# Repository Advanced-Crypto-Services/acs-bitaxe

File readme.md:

# **Based on the Bitaxe project**
## https://github.com/skot/bitaxe

# FIRST BATCH OF PCBS ORDERED 11/27/24

# Current Models
## Bitaxe Ultra 204 Modified for 800x480 add-on

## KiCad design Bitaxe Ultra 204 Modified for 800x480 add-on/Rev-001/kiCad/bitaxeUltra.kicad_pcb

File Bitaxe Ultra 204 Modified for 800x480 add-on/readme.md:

```
Open Source is Intrinsic to Bitcoin
```
# The bitaxeUltra
bitaxe is a fully open source hardware Bitcoin ASIC miner. Ultra is the 3rd major revision of the bitaxe that now includes the BM1366 ASIC from the S19XP

## Bitaxe Ultra 204 Modified for 800x480 add-on
- **This model is based on the Bitaxe Ultra 204 model, but modified for the 800x480 resolution of the add-on. Used with the following projects:**
- https://github.com/Advanced-Crypto-Services/acs-esp-miner
- https://github.com/Advanced-Crypto-Services/acs-bitaxe-lcd-800x480

### Modifications: 
- Added addtional i2C pins for the 800x480 LCD
- Added 4.7k pull-up resistors to the i2C pins for better signal integrity
- Added 5V_OUT for powering the LCD
- Added a Fuse on both 5V_OUT and V_IN
- Added third heatsink mounting hole for better stability with Tower Cooler
- Changed the BOOT and RESET buttons to 90 degree angled buttons for better access when inside and enclosure

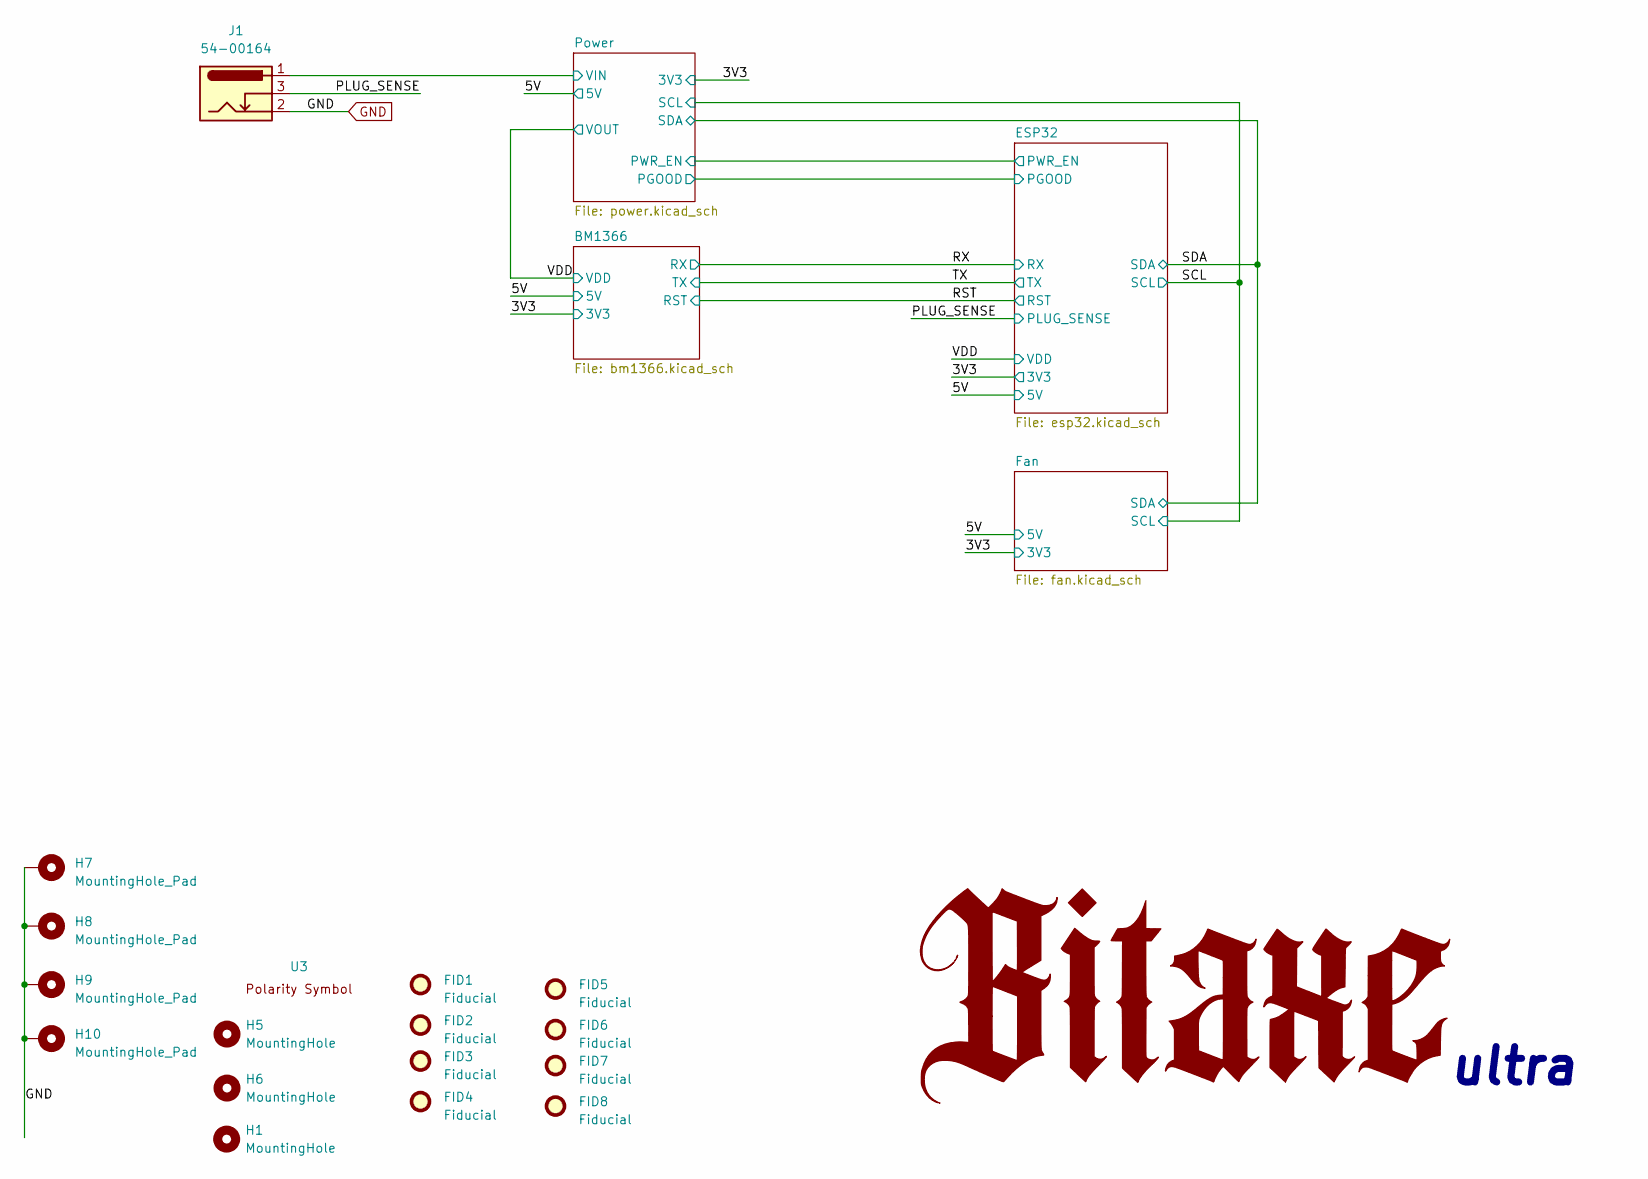
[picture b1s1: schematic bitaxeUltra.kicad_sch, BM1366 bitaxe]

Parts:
FID1, FID2, FID3, FID4, FID5, FID6, FID7, FID8: Fiducial; Fiducial_1mm_Mask2mm
H1, H5, H6: MountingHole; MountingHole_3.5mm
H7, H8, H9, H10: MountingHole_Pad; MountingHole_3mm_Pad_Via
J1: 54-00164; BarrelJack_Wuerth_694106106102_2.0x5.5mm; PARTNO 54-00164
U3: polarity

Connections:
/PLUG_SENSE: J1.3; also elsewhere on the board
/Power/VIN: J1.1; also elsewhere on the board
GND: H7.1, H8.1, H9.1, H10.1, J1.2; also elsewhere on the board

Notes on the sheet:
ultra

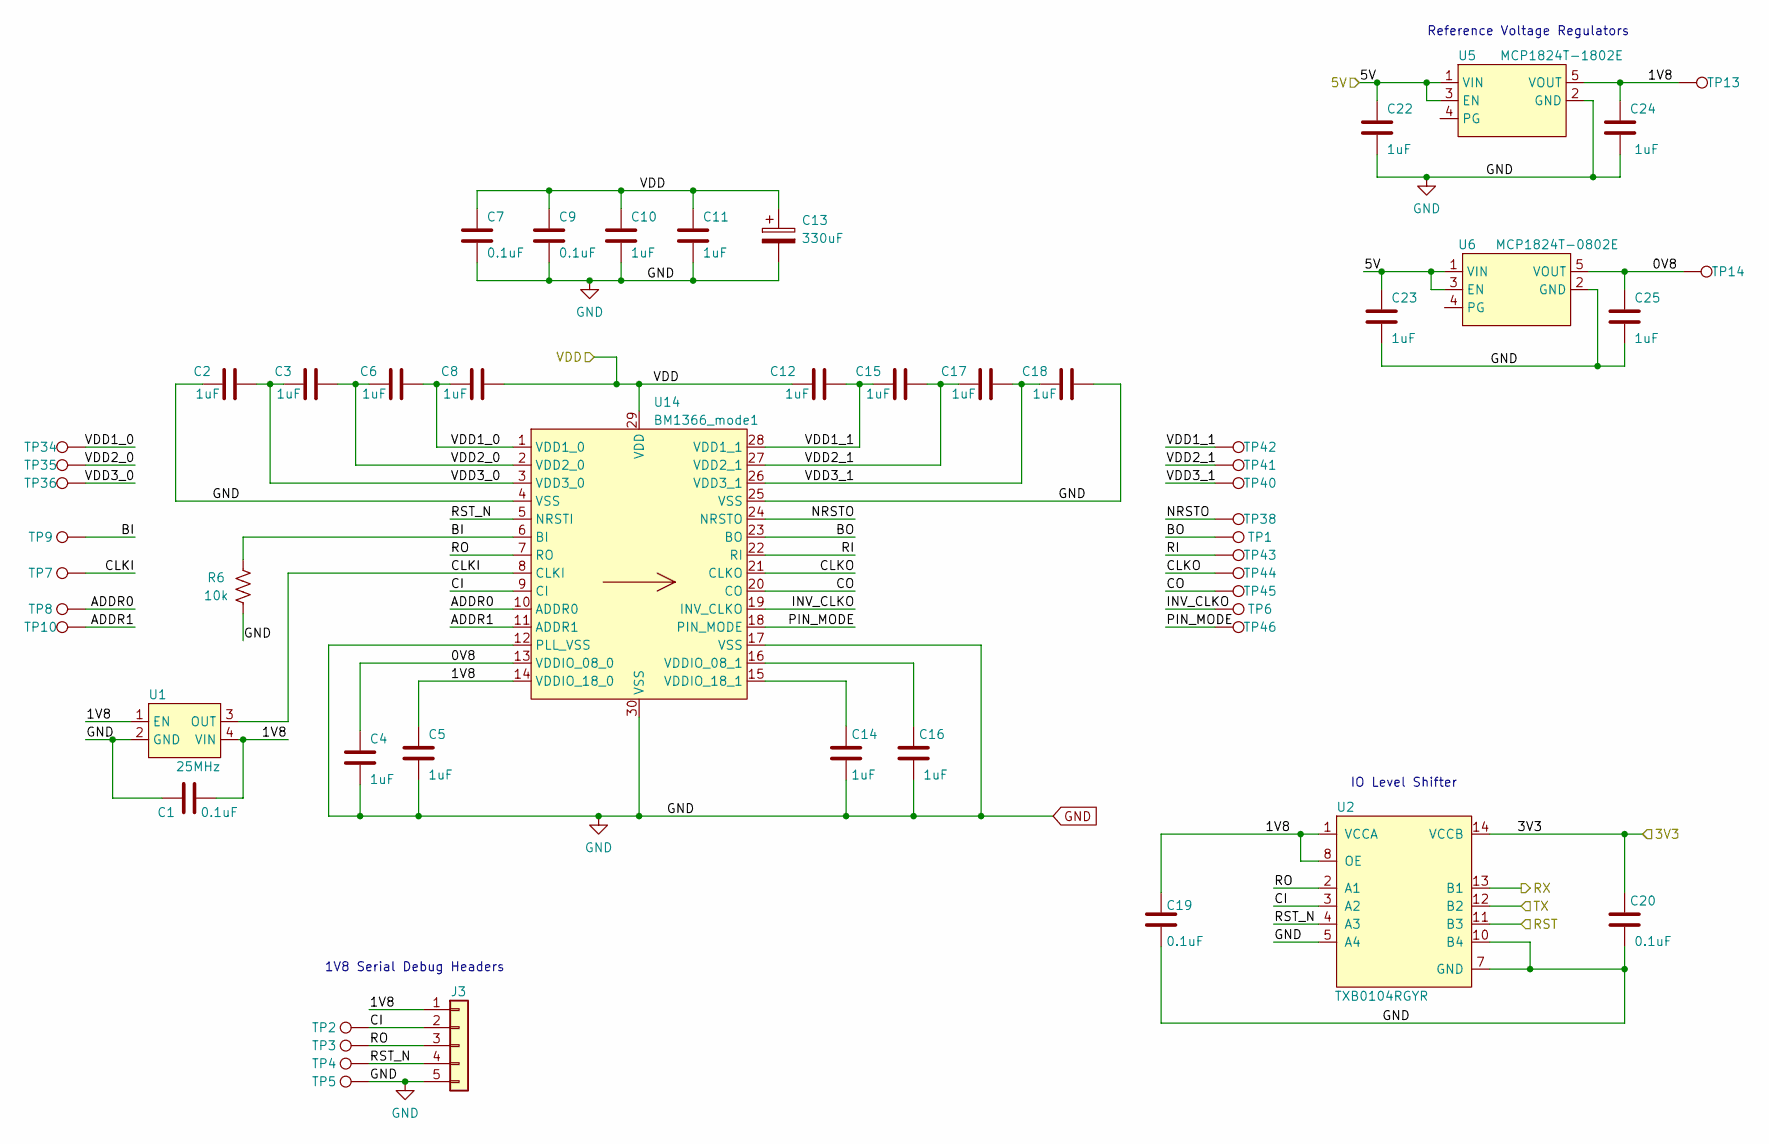
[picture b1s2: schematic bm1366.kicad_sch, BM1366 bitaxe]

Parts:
C1, C7, C9, C19, C20: 0.1uF; C_0402_1005Metric; PARTNO 0402X104K100CT
C2, C3, C4, C5, C6, C8, C10, C11, C12, C14, C15, C16, C17, C18, C22, C23, C24, C25: 1uF; C_0402_1005Metric; PARTNO EMK105BJ105MV-F
C13: 330uF; CP_EIA-7343-31_Kemet-D_Pad2.25x2.55mm_HandSolder; PARTNO 293D337X9010E2TE3
J3: Conn_01x05; PinHeader_1x05_P2.54mm_Vertical
R6: 10k; R_0402_1005Metric; PARTNO RC0402JR-0710KL
TP1, TP2, TP3, TP4, TP5, TP6, TP7, TP8, TP9, TP10, TP13, TP14, TP34, TP35, TP36, TP38, TP40, TP41, TP42, TP43, TP44, TP45, TP46: TestPoint; TestPoint_Pad_D1.5mm
U1: 25MHz; O 25,0-JO32-B-1V3-1-T1-LF; PARTNO O 25,0-JO32-B-1V3-1-T1-LF
U2: TXB0104RGYR; TXB0104; PARTNO TXB0104RGYR
U5: MCP1824T-1802E; SOT-23-5; PARTNO MCP1824T-1802E/OT
U6: MCP1824T-0802E; SOT-23-5; PARTNO MCP1824T-0802E/OT
U14: BM1366_mode1; BM1366

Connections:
/3V3: C20.1, U2.14 (VCCB); also elsewhere on the board
/5V: C22.1, C23.1, U5.1 (VIN), U5.3 (EN), U6.1 (VIN), U6.3 (EN); also elsewhere on the board
/BM1366/0V8: C4.1, C25.1, TP14.1, U6.5 (VOUT), U14.13 (VDDIO_08_0)
/BM1366/1V8: C1.2, C5.1, C19.1, C24.1, J3.1, TP13.1, U1.1 (EN), U1.4 (VIN), U2.1 (VCCA), U2.8 (OE), U5.5 (VOUT), U14.14 (VDDIO_18_0)
/BM1366/ADDR0: TP8.1, U14.10 (ADDR0)
/BM1366/ADDR1: TP10.1, U14.11 (ADDR1)
/BM1366/BI: R6.2, TP9.1, U14.6 (BI)
/BM1366/BO: TP1.1, U14.23 (BO)
/BM1366/CI: J3.2, TP2.1, U2.3 (A2), U14.9 (CI)
/BM1366/CLKI: TP7.1, U1.3 (OUT), U14.8 (CLKI)
/BM1366/CLKO: TP44.1, U14.21 (CLKO)
/BM1366/CO: TP45.1, U14.20 (CO)
/BM1366/INV_CLKO: TP6.1, U14.19 (INV_CLKO)
/BM1366/NRSTO: TP38.1, U14.24 (NRSTO)
/BM1366/PIN_MODE: TP46.1, U14.18 (PIN_MODE)
/BM1366/RI: TP43.1, U14.22 (RI)
/BM1366/RO: J3.3, TP3.1, U2.2 (A1), U14.7 (RO)
/BM1366/RST_N: J3.4, TP4.1, U2.4 (A3), U14.5 (NRSTI)
/BM1366/VDD1_0: C6.2, C8.1, TP34.1, U14.1 (VDD1_0)
/BM1366/VDD1_1: C12.2, C15.1, TP42.1, U14.28 (VDD1_1)
/BM1366/VDD2_0: C3.2, C6.1, TP35.1, U14.2 (VDD2_0)
/BM1366/VDD2_1: C15.2, C17.1, TP41.1, U14.27 (VDD2_1)
/BM1366/VDD3_0: C2.2, C3.1, TP36.1, U14.3 (VDD3_0)
/BM1366/VDD3_1: C17.2, C18.1, TP40.1, U14.26 (VDD3_1)
/RST: U2.11 (B3); also elsewhere on the board
/RX: U2.13 (B1); also elsewhere on the board
/TX: U2.12 (B2); also elsewhere on the board
/VDD: C7.1, C8.2, C9.1, C10.1, C11.1, C12.1, C13.1, U14.29 (VDD); also elsewhere on the board
GND: C1.1, C2.1, C4.2, C5.2, C7.2, C9.2, C10.2, C11.2, C13.2, C14.2, C16.2, C18.2, C19.2, C20.2, C22.2, C23.2, C24.2, C25.2, J3.5, R6.1, TP5.1, U1.2 (GND), U2.5 (A4), U2.7 (GND), U2.10 (B4), U2.15 (GND), U2.16 (GND), U2.17 (GND), U2.18 (GND), U2.19 (GND), U5.2 (GND), U6.2 (GND), U14.4 (VSS), U14.12 (PLL_VSS), U14.17 (VSS), U14.25 (VSS), U14.30 (VSS); also elsewhere on the board
unnamed: C16.1, U14.16 (VDDIO_08_1)
unnamed: C14.1, U14.15 (VDDIO_18_1)

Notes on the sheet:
1V8 Serial Debug Headers
Reference Voltage Regulators
IO Level Shifter

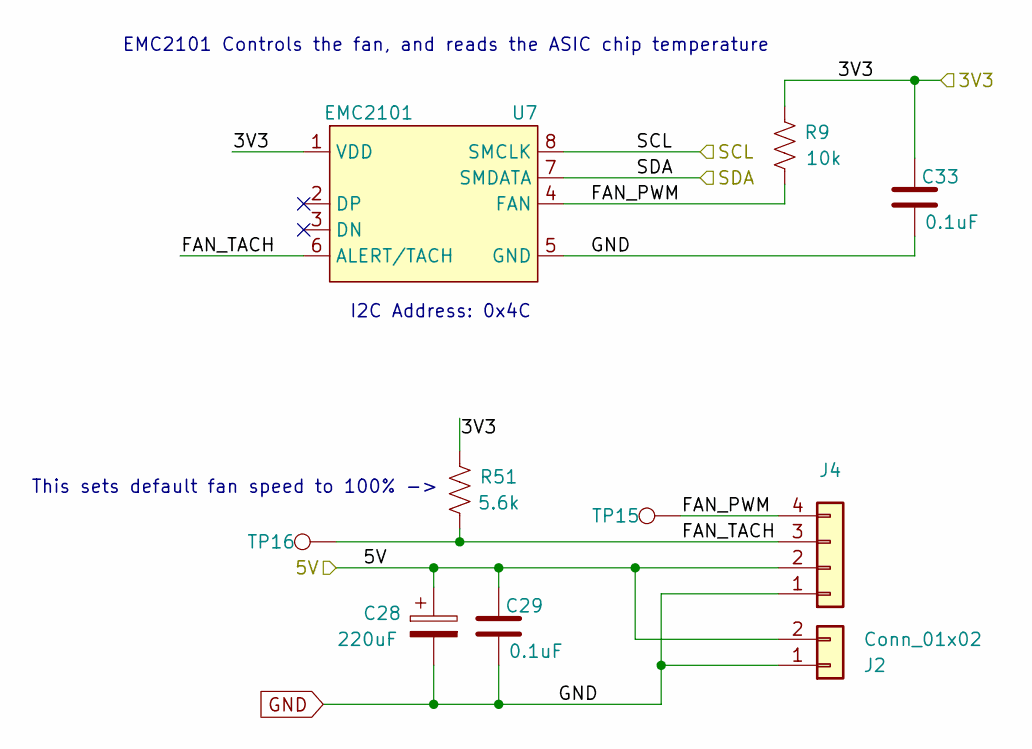
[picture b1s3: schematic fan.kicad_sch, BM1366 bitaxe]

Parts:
C28: 220uF; CP_Elec_6.3x7.7; PARTNO 865080345012
C29, C33: 0.1uF; C_0402_1005Metric; PARTNO 0402X104K100CT
J2: Conn_01x02; JST_XH_B2B-XH-A_1x02_P2.50mm_Vertical; PARTNO B2B-XH-A
J4: Conn_01x04; 470531000; PARTNO 0470531000
R9: 10k; R_0402_1005Metric; PARTNO RC0402JR-0710KL
R51: 5.6k; R_0402_1005Metric; PARTNO RC0402FR-135K6L
TP15, TP16: TestPoint; TestPoint_Pad_D1.5mm
U7: EMC2101; TSSOP-8_3x3mm_P0.65mm; PARTNO EMC2101-R-ACZL-TR

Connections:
/3V3: C33.1, R9.2, U7.1 (VDD); also elsewhere on the board
/5V: C28.1, C29.1, J2.2, J4.2; also elsewhere on the board
/Fan/FAN_PWM: J4.4, R9.1, TP15.1, U7.4 (FAN)
/Fan/FAN_TACH: J4.3, TP16.1, U7.6 (ALERT/TACH); also elsewhere on the board
/SCL: U7.8 (SMCLK); also elsewhere on the board
/SDA: U7.7 (SMDATA); also elsewhere on the board
GND: C28.2, C29.2, C33.2, J2.1, J4.1, U7.5 (GND); also elsewhere on the board

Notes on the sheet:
EMC2101 Controls the fan, and reads the ASIC chip temperature
This sets default fan speed to 100% ->
I2C Address: 0x4C

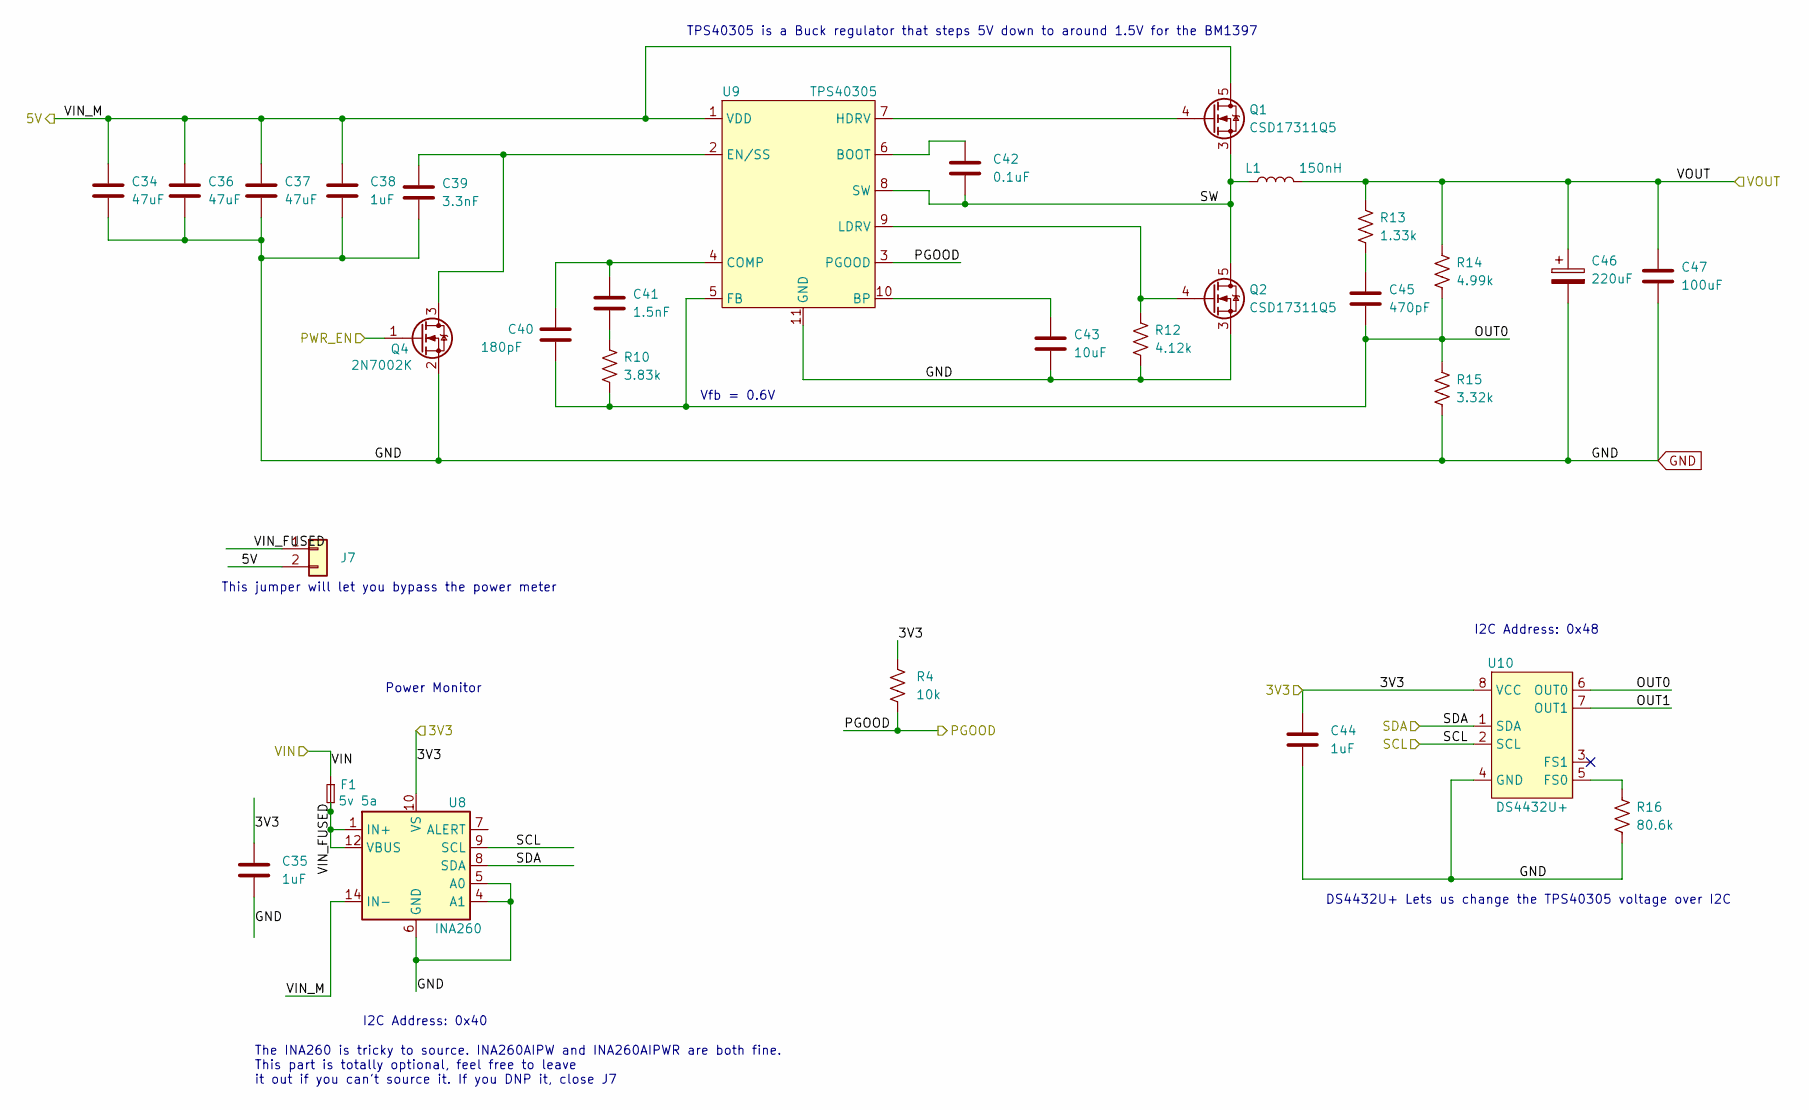
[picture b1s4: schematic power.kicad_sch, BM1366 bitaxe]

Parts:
C34, C36, C37: 47uF; C_1210_3225Metric; PARTNO GRM32ER61C476KE15L
C35, C44: 1uF; C_0402_1005Metric; PARTNO EMK105BJ105MV-F
C38: 1uF; C_0402_1005Metric; PARTNO CL21B105KOFNNNG
C39: 3.3nF; C_0402_1005Metric; PARTNO CL05B332KB5NNNC
C40: 180pF; C_0805_2012Metric; PARTNO CC0805JRNPO9BN181
C41: 1.5nF; C_0805_2012Metric; PARTNO CC0805KRX7R9BB152
C42: 0.1uF; C_0402_1005Metric; PARTNO 0402X104K100CT
C43: 10uF; C_0805_2012Metric; PARTNO CL21A106KOQNNNE
C45: 470pF; C_0805_2012Metric; PARTNO 0805B471K500CT
C46: 220uF; CAP_2R5TPE220MAFB; PARTNO 2R5TPE220MAFB
C47: 100uF; C_1206_3216Metric; PARTNO C3216X5R0J107M160AB
F1: 5v 5a; Fuse_0603_1608Metric
J7: Conn_01x02; PinHeader_1x02_P2.54mm_Vertical
L1: 150nH; FP1005R1-R15-R; PARTNO FP1005R1-R15-R
Q1, Q2: CSD17311Q5; PARTNO CSD17311Q5
Q4: 2N7002K; SOT-323_SC-70; PARTNO 2N7002KW
R4: 10k; R_0402_1005Metric; PARTNO RC0402JR-0710KL
R10: 3.83k; R_0402_1005Metric; PARTNO RC0402FR-073K83L
R12: 4.12k; R_0402_1005Metric; PARTNO RMCF0402FT4K12
R13: 1.33k; R_0402_1005Metric; PARTNO RC0402FR-071K33L
R14: 4.99k; R_0402_1005Metric; PARTNO RC0402FR-074K99L
R15: 3.32k; R_0402_1005Metric; PARTNO RC0402FR-073K32L
R16: 80.6k; R_0402_1005Metric; PARTNO RC0402FR-0780K6L
U8: INA260; TSSOP-16_4.4x5mm_P0.65mm; PARTNO INA260AIPW
U9: TPS40305; PARTNO TPS40305DRCR
U10: DS4432U+; TSSOP-8_3x3mm_P0.65mm; PARTNO DS4432U+

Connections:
/3V3: C35.1, C44.1, R4.1, U8.10 (VS), U10.8 (VCC); also elsewhere on the board
/5V: C34.1, C36.1, C37.1, C38.1, J7.2, Q1.5 (D), U8.14 (IN-), U8.15 (IN-), U8.16 (IN-), U9.1 (VDD); also elsewhere on the board
/ESP32/PWR_EN: Q4.1 (G); also elsewhere on the board
/Power/OUT0: C40.2, C45.2, R10.2, R14.2, R15.1, U9.5 (FB), U10.6 (OUT0)
/Power/OUT1: U10.7 (OUT1)
/Power/PGOOD: R4.2, U9.3 (PGOOD); also elsewhere on the board
/Power/SW: C42.2, L1.1, Q1.1, Q1.2, Q1.3 (S), Q2.5 (D), U9.8 (SW)
/Power/VIN: F1.1; also elsewhere on the board
/Power/VIN_FUSED: F1.2, J7.1, U8.1 (IN+), U8.2 (IN+), U8.3 (IN+), U8.12 (VBUS)
/SCL: U8.9 (SCL), U10.2 (SCL); also elsewhere on the board
/SDA: U8.8 (SDA), U10.1 (SDA); also elsewhere on the board
/VDD: C46.1, C47.1, L1.2, R13.1, R14.1; also elsewhere on the board
GND: C34.2, C35.2, C36.2, C37.2, C38.2, C39.2, C43.2, C44.2, C46.2, C47.2, Q2.1, Q2.2, Q2.3 (S), Q4.2 (S), R12.2, R15.2, R16.2, U8.4 (A1), U8.5 (A0), U8.6 (GND), U8.11 (GND), U9.11 (GND), U10.4 (GND); also elsewhere on the board
unnamed: C41.2, R10.1
unnamed: C45.1, R13.2
unnamed: Q1.4 (G), U9.7 (HDRV)
unnamed: Q2.4 (G), R12.1, U9.9 (LDRV)
unnamed: C39.1, Q4.3 (D), U9.2 (EN/SS)
unnamed: C42.1, U9.6 (BOOT)
unnamed: C43.1, U9.10 (BP)
unnamed: C40.1, C41.1, U9.4 (COMP)
unnamed: R16.1, U10.5 (FS0)

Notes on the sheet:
DS4432U+ Lets us change the TPS40305 voltage over I2C
I2C Address: 0x48
The INA260 is tricky to source. INA260AIPW and INA260AIPWR are both fine. This part is totally optional, feel free to leave it out if you can't source it. If you DNP it, close J7
Power Monitor
TPS40305 is a Buck regulator that steps 5V down to around 1.5V for the BM1397
I2C Address: 0x40
Vfb = 0.6V
This jumper will let you bypass the power meter

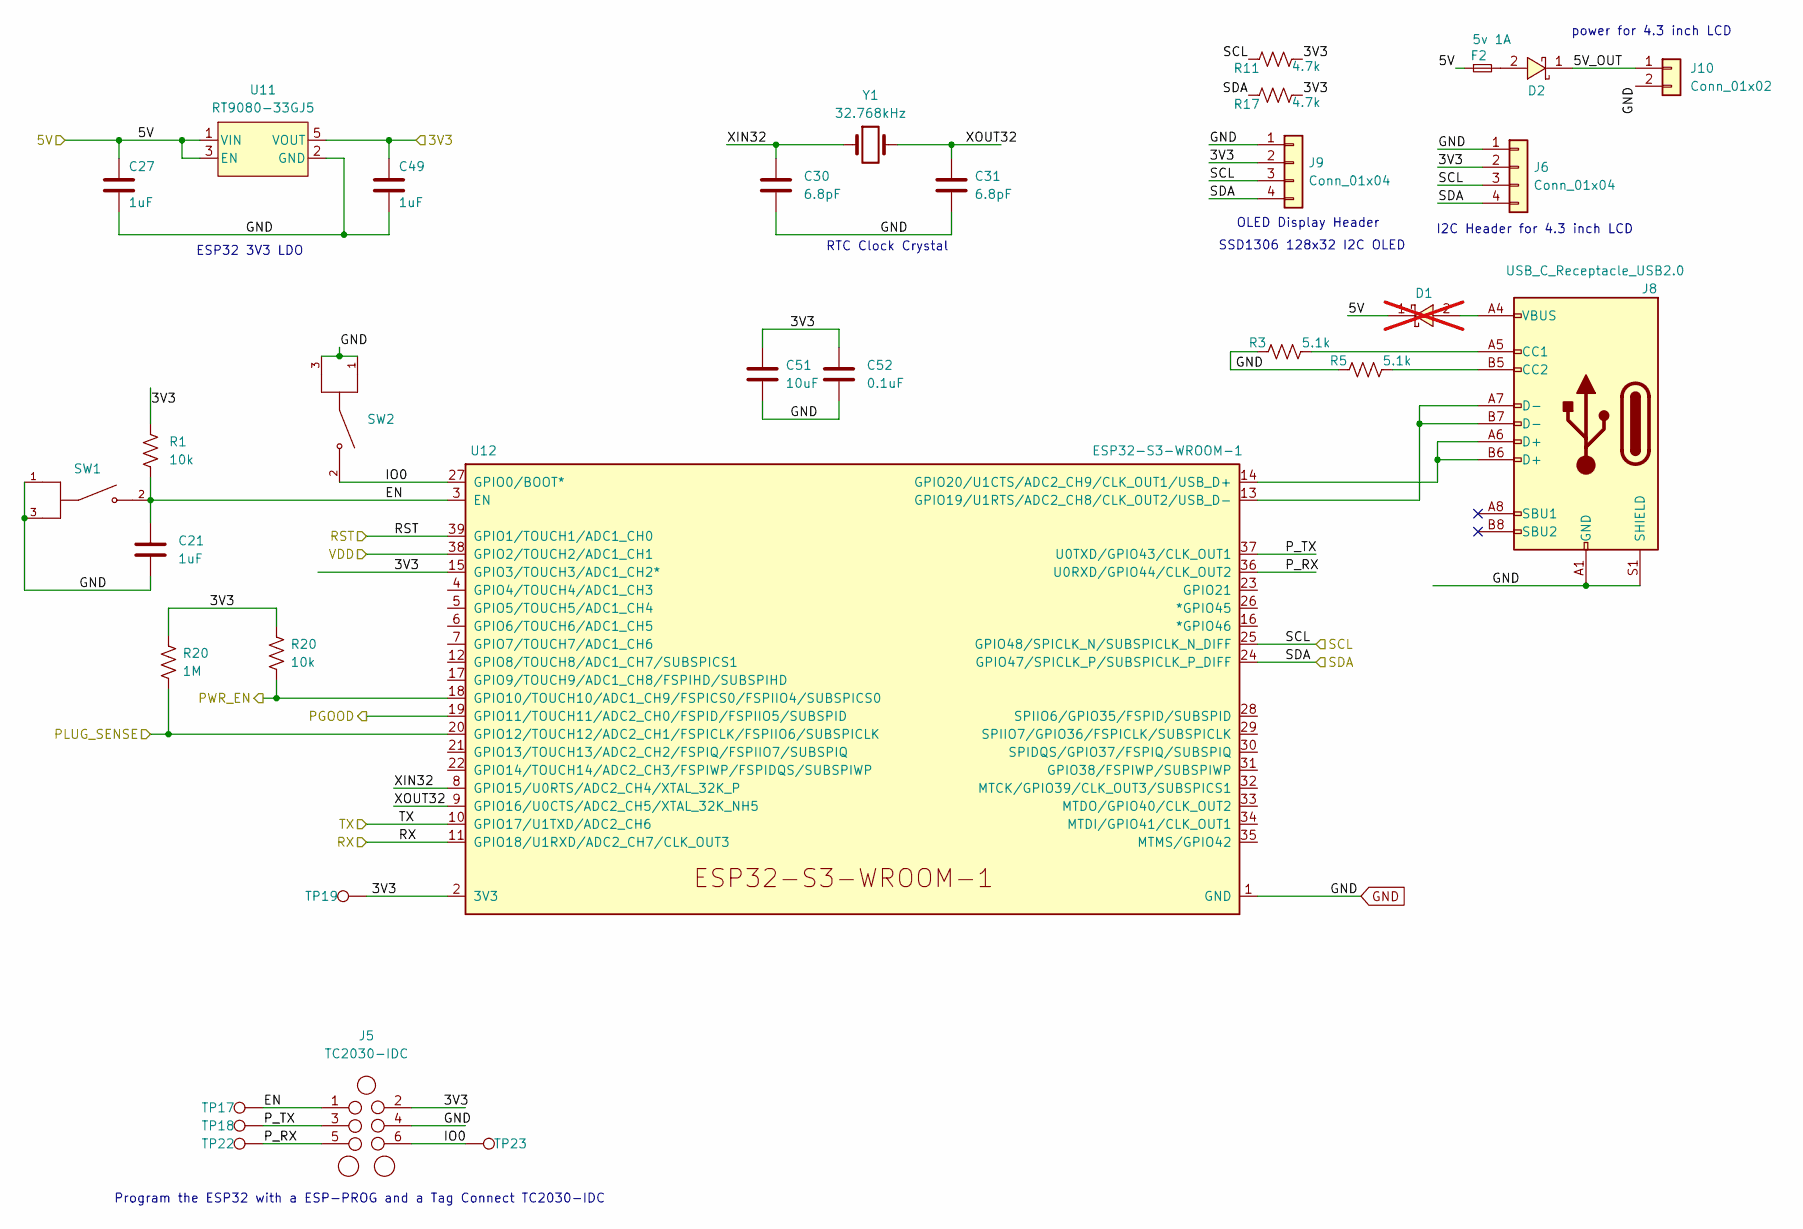
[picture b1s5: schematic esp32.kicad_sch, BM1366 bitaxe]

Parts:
C21, C27, C49: 1uF; C_0402_1005Metric; PARTNO EMK105BJ105MV-F
C30, C31: 6.8pF; C_0402_1005Metric; PARTNO C0402C689C5GAC7867
C51: 10uF; C_0805_2012Metric; PARTNO CL21A106KOQNNNE
C52: 0.1uF; C_0402_1005Metric; PARTNO 0402X104K100CT
D1: SS310; D_SMA; PARTNO SK310A-LTP; not fitted
D2: SS310; D_SMA; PARTNO SK310A-LTP
F2: 5v 1A; Fuse_0603_1608Metric
J5: TC2030-IDC; Tag-Connect_TC2030-IDC-NL_2x03_P1.27mm_Vertical
J6, J9: Conn_01x04; PinSocket_1x04_P2.54mm_Vertical
J8: USB_C_Receptacle_USB2.0; USB_C_Receptacle_GCT_USB4105-xx-A_16P_TopMnt_Horizontal; PARTNO USB4105-GF-A
J10: Conn_01x02; PinSocket_1x02_P2.54mm_Vertical
R1: 10k; R_0402_1005Metric; PARTNO RC0402JR-0710KL
R3, R5: 5.1k; R_0402_1005Metric; PARTNO RMCF0402JT5K10
R11, R17: 4.7k; R_0402_1005Metric; PARTNO RMCF0402JT5K10
R20: 1M; R_0402_1005Metric; PARTNO RC0402FR-071ML
SW1, SW2: GT-TC029B-H025-L1N; SW_TL3340AF160QG; PARTNO CS1213AGF260
TP17, TP18, TP19, TP22, TP23: TestPoint; TestPoint_Pad_D1.5mm
U11: RT9080-33GJ5; PARTNO RT9080-33GJ5
U12: ESP32-S3-WROOM-1; PARTNO ESP32-S3-WROOM-1-N16R8
Y1: 32.768kHz; SC32S-7PF20PPM; PARTNO SC32S-7PF20PPM

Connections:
/3V3: C49.1, C51.1, C52.1, J5.2, J6.2, J9.2, R1.1, R11.2, R17.2, TP19.1, U11.5 (VOUT), U12.2 (3V3), U12.15 (GPIO3/TOUCH3/ADC1_CH2*); also elsewhere on the board
/5V: C27.1, D1.1, F2.1, U11.1 (VIN), U11.3 (EN); also elsewhere on the board
/ESP32/5V_OUT: D2.1, J10.1
/ESP32/EN: C21.1, J5.1, R1.2, SW1.2, TP17.1, U12.3 (EN)
/ESP32/IO0: J5.6, SW2.2, TP23.1, U12.27 (GPIO0/BOOT*)
/ESP32/PWR_EN: U12.18 (GPIO10/TOUCH10/ADC1_CH9/FSPICS0/FSPIIO4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); also elsewhere on the board
/ESP32/P_RX: J5.5, TP22.1, U12.36 (U0RXD/GPIO44/CLK_OUT2)
/ESP32/P_TX: J5.3, TP18.1, U12.37 (U0TXD/GPIO43/CLK_OUT1)
/ESP32/XIN32: C30.1, U12.8 (GPIO15/U0RTS/ADC2_CH4/XTAL_32K_P), Y1.1
/ESP32/XOUT32: C31.1, U12.9 (GPIO16/U0CTS/ADC2_CH5/XTAL_32K_NH5), Y1.2
/PLUG_SENSE: U12.20 (GPIO12/TOUCH12/ADC2_CH1/FSPICLK/FSPIIO6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); also elsewhere on the board
/Power/PGOOD: U12.19 (GPIO11/TOUCH11/ADC2_CH0/FSPID/FSPIIO5/S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); also elsewhere on the board
/RST: U12.39 (GPIO1/TOUCH1/ADC1_CH0); also elsewhere on the board
/RX: U12.11 (GPIO18/U1RXD/ADC2_CH7/CLK_OUT3); also elsewhere on the board
/SCL: J6.3, J9.3, R11.1, U12.25 (GPIO48/SPICLK_N/SUBSPICLK_N_DIFF); also elsewhere on the board
/SDA: J6.4, J9.4, R17.1, U12.24 (GPIO47/SPICLK_P/SUBSPICLK_P_DIFF); also elsewhere on the board
/TX: U12.10 (GPIO17/U1TXD/ADC2_CH6); also elsewhere on the board
/VDD: U12.38 (GPIO2/TOUCH2/ADC1_CH1); also elsewhere on the board
GND: C21.2, C27.2, C30.2, C31.2, C49.2, C51.2, C52.2, J5.4, J6.1, J8.A1 (GND), J8.A12 (GND), J8.B1 (GND), J8.B12 (GND), J8.S1 (SHIELD), J9.1, J10.2, R3.1, R5.1, SW1.1, SW1.3, SW2.1, SW2.3, U11.2 (GND), U12.1 (GND), U12.40 (GND), U12.41 (GND); also elsewhere on the board
unnamed: D1.2, J8.A4 (VBUS), J8.A9 (VBUS), J8.B4 (VBUS), J8.B9 (VBUS)
unnamed: D2.2, F2.2
unnamed: J8.A5 (CC1), R3.2
unnamed: J8.B5 (CC2), R5.2
unnamed: J8.A7 (D-), J8.B7 (D-), U12.13 (GPIO19/U1RTS/ADC2_CH8/CLK_OUT2/USB_D-)
unnamed: J8.A6 (D+), J8.B6 (D+), U12.14 (GPIO20/U1CTS/ADC2_CH9/CLK_OUT1/USB_D+)

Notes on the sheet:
I2C Header for 4.3 inch LCD
RTC Clock Crystal
ESP32 3V3 LDO
Program the ESP32 with a ESP-PROG and a Tag Connect TC2030-IDC
SSD1306 128x32 I2C OLED
power for 4.3 inch LCD
OLED Display Header

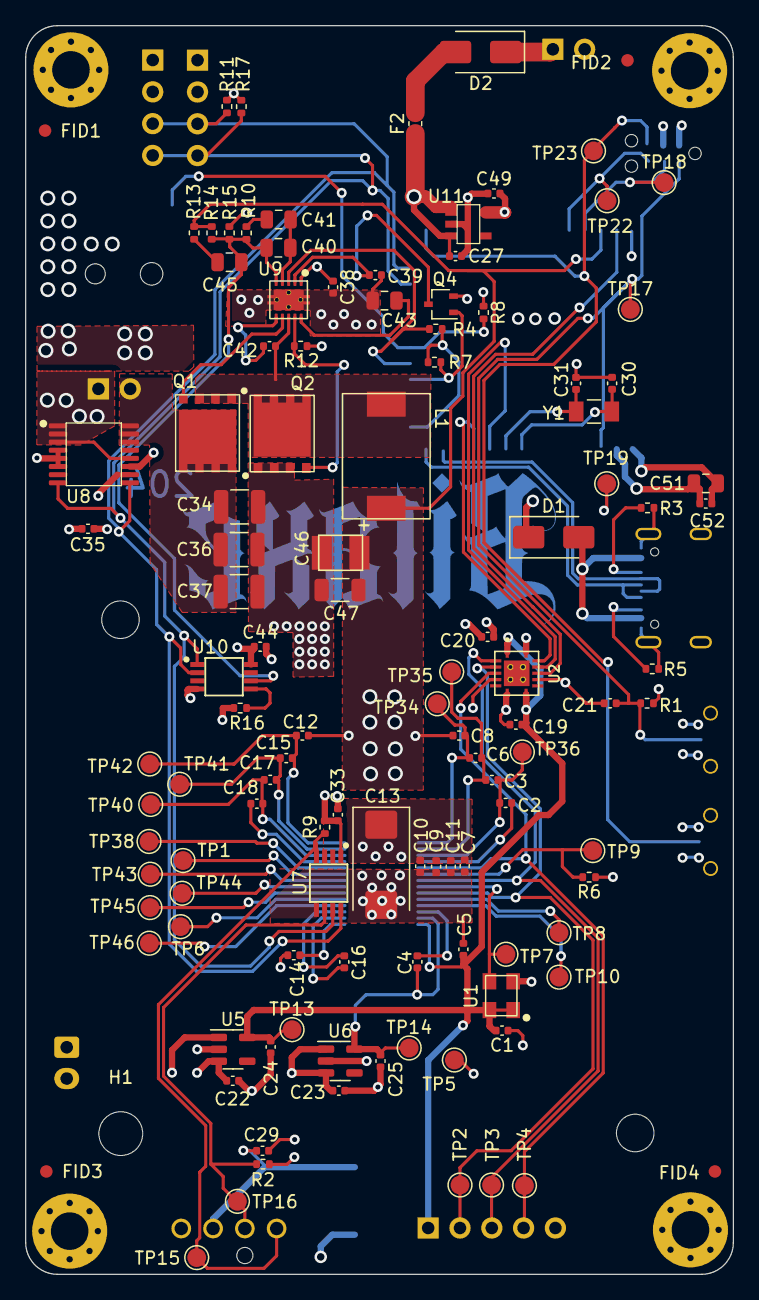
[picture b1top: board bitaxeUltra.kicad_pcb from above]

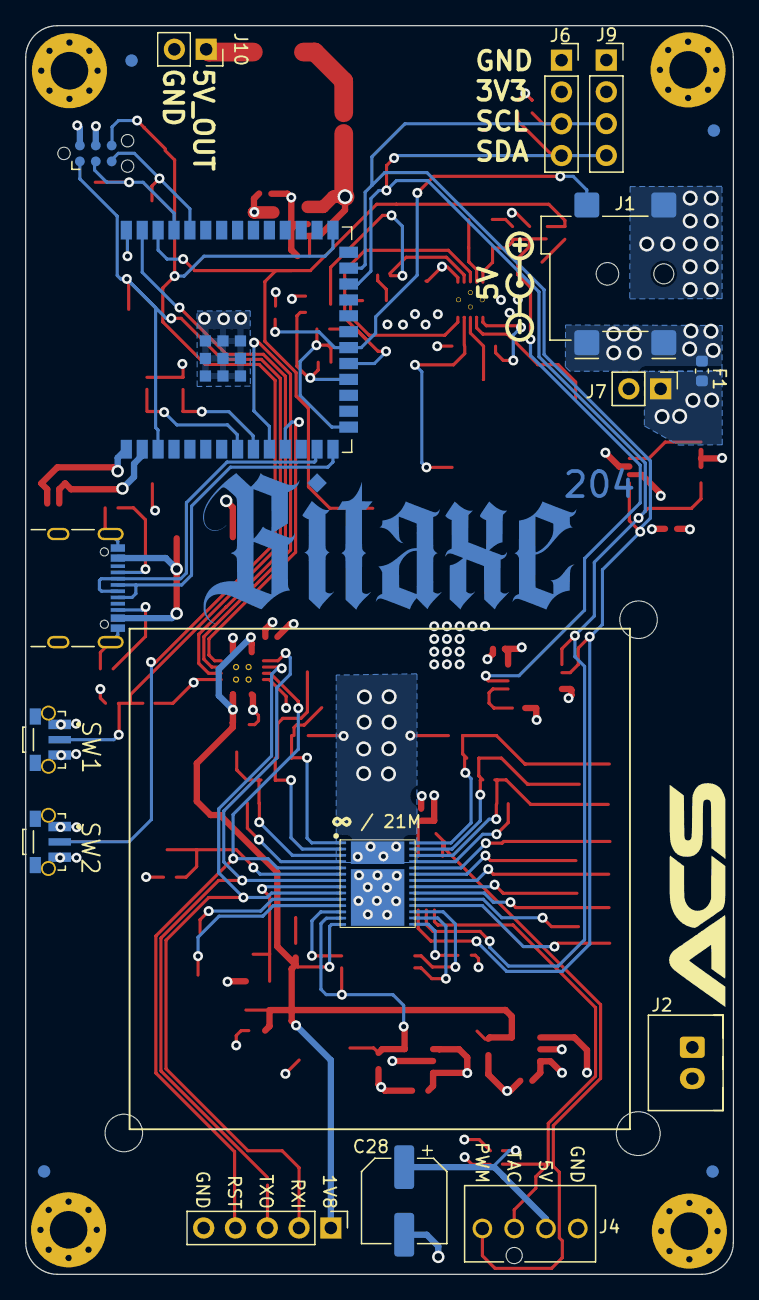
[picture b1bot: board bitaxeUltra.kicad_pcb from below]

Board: 4 copper layers, 56.5 x 99.8 mm, 143 parts (21 on the bottom side), 64 nets.

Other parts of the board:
R2: 5.6k; R_0402_1005Metric
R7: 10k; R_0402_1005Metric
R8: 1M; R_0402_1005Metric

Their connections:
/3V3: R2.2, R7.1, R8.1; also elsewhere on the board
/ESP32/PWR_EN: R7.2; also elsewhere on the board
/Fan/FAN_TACH: R2.1; also elsewhere on the board
/PLUG_SENSE: R8.2; also elsewhere on the board

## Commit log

2024-11-27 Init Commit - Bitaxe Ultra 204
2024-11-27 added read me
2024-11-28 autosave
2024-11-30 added solder points to hold down reset button
2024-12-09 Create Bitaxe Touch Case
2024-12-10 Changed DC barrel jack port dimensions
    Changed DC barrel jack port dimensions
2024-12-10 BitaxeCaseUltraFianal
2024-12-12 Updated various fitment issues
2024-12-13 Redesign cooling
2024-12-13 Added option for second fan and improved airflow
2024-12-14 Improved cooling-dual fan option.
2025-01-12 Case design Change
    Old design had a lot of overheating issues, redesign takes care of that.
    Final Version: Skel V6
2025-01-26 update read mes
